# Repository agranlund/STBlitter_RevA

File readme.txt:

----------------------------------------------------------------

A simple Blitter + IDE + 256k ROM decoding board for Atari ST(M)
(c) 2019 Anders Granlund
agranlund@gmail.com

www.happydaze.se

----------------------------------------------------------------

IDE and ROM functionality is based on the work of P.Putnik:
http://atari.8bitchip.info/astide.php

----------------------------------------------------------------

This hardware is provided 'as-is', without any express
or implied warranty. In no event will the authors be held
liable for any damages arising from the use of this hardware.

----------------------------------------------------------------

Notes:

* There are no dependencies between Blitter and ROM+IDE functionality so you can easily
  make a Blitter-only board by leaving out the other parts, or vice versa.

* Bridge 2-3 on both JP1 & JP2 when blitter chip is fitted

* Bridge 1-2 on both JP1 & JP2 when no blitter chip is fitted

* Solder-jumpers SJ1 & SJ2 must always be bridged.
  These are located directly below jumpers JP1 & JP2.

* Resistor R8 is optional and should normally NOT be used.
  If it is used, you must remove Atari ST motherboard resistor R4.
  Atari resistor R4 is a pullup for blitter interrupt (INT3).
  On the ST, this is a 4K7 resistor but on STFM/Mega/STE it has a value of 1K.
  My STBlitter works fine without having to change anything on the ST motherboard,
  but if yours is not then you might want to try changing Atari resistor R4 to a 1K resistor instead.
  Alternatively, just remove it from the Atari and fit a 1K resistor as R8 on STBlitter board.

* EmuTos 0.9.11 will take a very long time to boot if there is no IDE drive is connected.
  This is not a problem on Atari TOS. Nor is it a problem on EmuTos if you have a drive connected.

* The IDE bus is NOT buffered so if you must use cables you need to keep them very short.
  I am using a CF adapter directly plugged into the board without cables and this works fast and reliable.

* The main metal shielding in your ST will probably not fit unless you cut some chunks out of it.
  Perhaps it might fit if you solder the STBlitter directly to the ST motherboard instead of using a socket,
  but I have not tried that - I just run my ST without the metal shielding.

* You will have clearance issues if you are using the 4MB RAM upgrade from Exxos (the one that clips onto the MMU)
  You can solve this by either cutting a small chunk out of the 4MB Ram PCB using a dremel.
  (Make sure to check the underside so you know where the nearest traces are and how much you can cut!)
  Or just stack 2 CPU sockets on the ST motherboard to gain some height and clearance that way.

* The PCB is made from 4 layers according to design rules of Elecrow PCB service (www.elecrow.com)
  The exported Gerbers were done so according to how Elecrow want them so they may or may not be directly
  acceptable to other PCB manufacturers.

Installation:
---------------------------------------------------------------

- Desolder CPU from Atari motherboard and fit a 0.9" DIP4 socket instead.
  CPU is instead installed on the STBlitter board

- IDE: Wire from STBlitter-ACSI10 to pin 10 of ACSI interface (J2) on Atari ST motherboard

- Blitter: Wire from STBlitter-BIRQ to pin 25 of 68901 (U11) on Atari ST motherboard (or the correct side of
  the nearby resistor R4 if you rather solder to that)

- ROM decoding:
  Wiring for 256k ROM decoding will depend on how you modded your ST to fit 256k 2chip roms.
  Of course, you can ignore this step if you don't need ROM decoding or if you already have it from another expansion board.

- Wire from STBlitter-RCEI to ROM2 or CE from Glue.

- Wire from STBlitter-RCEO to CE for the ROMS.

I am using a self made Tos ROM board for holding the EEPROMS:
https://github.com/agranlund/STRom

Parts:
---------------------------------------------------------------

-- Common --
C3, C4        : 0.1uF
CPU Socket    : 2x 0.9" DIP64, digikey: ED90061-ND
ST connector  : 2x 32pin lathed male headers for connecting to socket on ST motherboard
                I use these, but you can of course find them on Digikey or elsewhere:
                https://www.electrokit.com/en/product/male-header-1x40p-lathed-breakable/
Pin headers   : Standard 2.52mm male headers for JP1, JP2 and (ACSI,RCEO,RECI,BIRQ) connector.
                (or ignore this and just solder instead)
Pin Jumper    : 2p jumper for JP1 & JP2 each    
                (or ignore this and just solder instead)

-- Blitter --

R8            : - DO NOT USE -
R1, R2        : 4K7
C1, C2        : 0.1uF
Socket        : PLCC68, digikey: AE10059-ND
Blitter       : You need to find a blitter from somewhere, for example from Exxos:
                https://www.exxoshost.co.uk/atari/last/storenew/

-- IDE & ROM decoding --

74LS03V       : DIP14 package
ATF16V8       : DIP20 package
C5, C6        : 0.1uF
R3            : 4K7
R4, R7        : 2K2
R5            : R390
R6            : R100
LED           : 3mm size
Header        : 2x44-2mm, Digikey: WM18853-ND

CUPL logic for ATF16V8:
----------------------------------------------

Name     STBlitter ;
PartNo   00 ;
Date     2019-09-03 ;
Revision 01 ;
Designer Anders Granlund ;
Company  HappyDaze ;
Assembly None ;
Location  ;
Device   g16v8 ;

/*
 A23     I [ 1     20 ] VCC 
 A22     I [ 2     19 ] T*    RCEI
 A21     I [ 3     18 ] T     RCEO
 A20     I [ 4     17 ] T     DTACK
 A19     I [ 5     16 ] T     IDE_WR
 A18     I [ 6     15 ] T     IDE_RD
 A17     I [ 7     14 ] T     IDE_CS1
 A16     I [ 8     13 ] T     IDE_CS0
 A5      I [ 9     12 ] T*    RW
       GND [ 10    11 ] I     AS
*/

/************ Inputs ************/

pin 1 = A23;
pin 2 = A22;
pin 3 = A21;
pin 4 = A20;
pin 5 = A19;
pin 6 = A18;
pin 7 = A17;
pin 8 = A16;
pin 9 = A5;
pin 11 = AS;
pin 12 = RW;
pin 19 = RCEI; 

/************ Outputs ************/

pin 13 = !IDE_CS0;
pin 14 = !IDE_CS1;
pin 15 = !IDE_RD;
pin 16 = !IDE_WR;
pin 17 = DTACK;
pin 18 = !RCEO;

/************ Logic ************/

DTACK = (!AS & A23 & A22 & A21 & !A20 & !A19 & !A18 & RW) # (A23 & A22 & A21 & A20 & !A19 & !A18 & !A17 & !A16);

RCEO = (!AS & A23 & A22 & A21 & !A20 & !A19 & !A18 & RW) # !RCEI;

IDE_CS0 = (A23 & A22 & A21 & A20 & !A19 & !A18 & !A17 & !A16 & !A5);
IDE_CS1 = (A23 & A22 & A21 & A20 & !A19 & !A18 & !A17 & !A16 & A5);

IDE_RD = (!AS & A23 & A22 & A21 & A20 & !A19 & !A18 & !A17 & !A16 & RW);
IDE_WR = (!AS & A23 & A22 & A21 & A20 & !A19 & !A18 & !A17 & !A16 & !RW);

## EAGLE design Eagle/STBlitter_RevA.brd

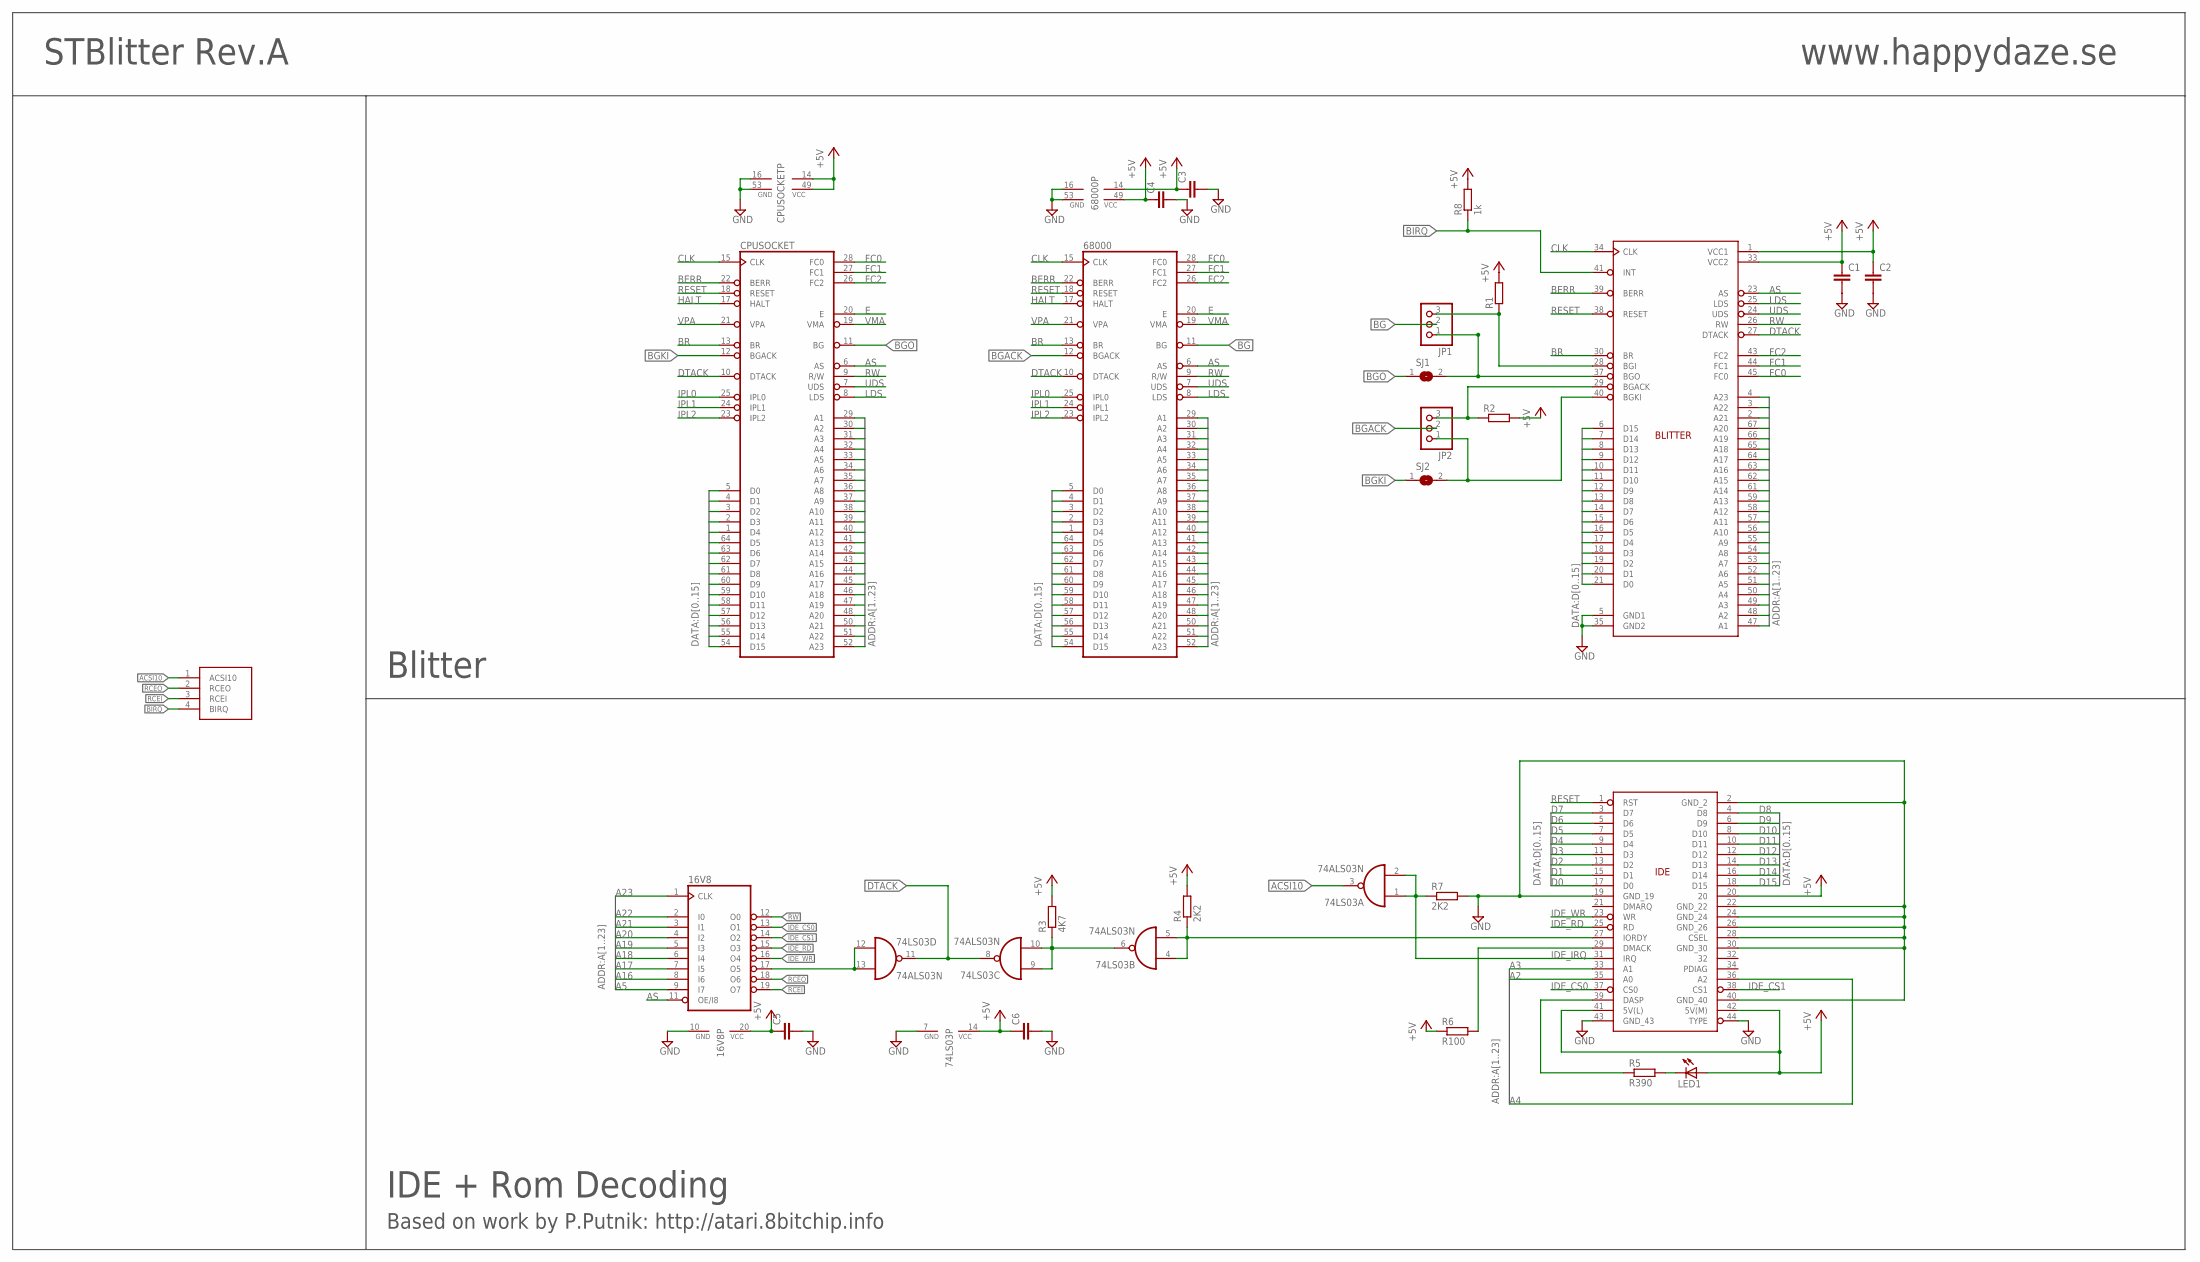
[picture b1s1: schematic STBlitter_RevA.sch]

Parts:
16V8: 16V8; DIL20
74LS03: 74ALS03N; DIL14
68000: MC68000P; DIL64
C1, C2, C3, C4, C5, C6: C-EU050-025X075; C050-025X075
CFCARD: IDE44_CON
CPUSOCKET: MC68000P; DIL64
JP1, JP2: PINHD-1X3; 1X03
LED1: LED3MM
R1, R2: R-EU_0207/12; 0207/12
R3: 4K7; 0207/12
R4, R7: 2K2; 0207/12
R5: R390; 0207/12
R6: R100; 0207/12
R8: 1k; 0207/12
SJ1, SJ2: SJ
U$1: STBLITTER; S68
U$2: XCON

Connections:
+5V: 16V8.20 (VCC), 74LS03.14 (VCC), 68000.14 (VCC), 68000.49 (VCC), C1.1, C2.1, C3.1, C4.1, C5.1, C6.1, CFCARD.20, CFCARD.41 (5V(L)), CFCARD.42 (5V(M)), CPUSOCKET.14 (VCC), CPUSOCKET.49 (VCC), LED1.A, R1.2, R2.2, R3.2, R4.2, R6.1, R8.2, U$1.1 (VCC1), U$1.33 (VCC2)
A1: 68000.29 (A1), CPUSOCKET.29 (A1), U$1.47 (A1)
A2: 68000.30 (A2), CFCARD.35 (A0), CPUSOCKET.30 (A2), U$1.48 (A2)
A3: 68000.31 (A3), CFCARD.33 (A1), CPUSOCKET.31 (A3), U$1.49 (A3)
A4: 68000.32 (A4), CFCARD.36 (A2), CPUSOCKET.32 (A4), U$1.50 (A4)
A5: 16V8.9 (I7), 68000.33 (A5), CPUSOCKET.33 (A5), U$1.51 (A5)
A6: 68000.34 (A6), CPUSOCKET.34 (A6), U$1.52 (A6)
A7: 68000.35 (A7), CPUSOCKET.35 (A7), U$1.53 (A7)
A8: 68000.36 (A8), CPUSOCKET.36 (A8), U$1.54 (A8)
A9: 68000.37 (A9), CPUSOCKET.37 (A9), U$1.55 (A9)
A10: 68000.38 (A10), CPUSOCKET.38 (A10), U$1.56 (A10)
A11: 68000.39 (A11), CPUSOCKET.39 (A11), U$1.57 (A11)
A12: 68000.40 (A12), CPUSOCKET.40 (A12), U$1.58 (A12)
A13: 68000.41 (A13), CPUSOCKET.41 (A13), U$1.59 (A13)
A14: 68000.42 (A14), CPUSOCKET.42 (A14), U$1.61 (A14)
A15: 68000.43 (A15), CPUSOCKET.43 (A15), U$1.62 (A15)
A16: 16V8.8 (I6), 68000.44 (A16), CPUSOCKET.44 (A16), U$1.63 (A16)
A17: 16V8.7 (I5), 68000.45 (A17), CPUSOCKET.45 (A17), U$1.64 (A17)
A18: 16V8.6 (I4), 68000.46 (A18), CPUSOCKET.46 (A18), U$1.65 (A18)
A19: 16V8.5 (I3), 68000.47 (A19), CPUSOCKET.47 (A19), U$1.66 (A19)
A20: 16V8.4 (I2), 68000.48 (A20), CPUSOCKET.48 (A20), U$1.67 (A20)
A21: 16V8.3 (I1), 68000.50 (A21), CPUSOCKET.50 (A21), U$1.2 (A21)
A22: 16V8.2 (I0), 68000.51 (A22), CPUSOCKET.51 (A22), U$1.3 (A22)
A23: 16V8.1 (CLK), 68000.52 (A23), CPUSOCKET.52 (A23), U$1.4 (A23)
ACSI10: 74LS03.3 (O), U$2.1 (ACSI10)
AS: 16V8.11 (OE/I8), 68000.6 (AS), CPUSOCKET.6 (AS), U$1.23 (AS)
BERR: 68000.22 (BERR), CPUSOCKET.22 (BERR), U$1.39 (BERR)
BG: 68000.11 (BG), JP1.2
BGACK: 68000.12 (BGACK), JP2.2
BGKI: CPUSOCKET.12 (BGACK), SJ2.1
BGO: CPUSOCKET.11 (BG), SJ1.1
BIRQ: R8.1, U$1.41 (INT), U$2.4 (BIRQ)
BLTBGI: JP1.3, R1.1, U$1.28 (BGI)
BR: 68000.13 (BR), CPUSOCKET.13 (BR), U$1.30 (BR)
CLK: 68000.15 (CLK), CPUSOCKET.15 (CLK), U$1.34 (CLK)
D0: 68000.5 (D0), CFCARD.17 (D0), CPUSOCKET.5 (D0), U$1.21 (D0)
D1: 68000.4 (D1), CFCARD.15 (D1), CPUSOCKET.4 (D1), U$1.20 (D1)
D2: 68000.3 (D2), CFCARD.13 (D2), CPUSOCKET.3 (D2), U$1.19 (D2)
D3: 68000.2 (D3), CFCARD.11 (D3), CPUSOCKET.2 (D3), U$1.18 (D3)
D4: 68000.1 (D4), CFCARD.9 (D4), CPUSOCKET.1 (D4), U$1.17 (D4)
D5: 68000.64 (D5), CFCARD.7 (D5), CPUSOCKET.64 (D5), U$1.16 (D5)
D6: 68000.63 (D6), CFCARD.5 (D6), CPUSOCKET.63 (D6), U$1.15 (D6)
D7: 68000.62 (D7), CFCARD.3 (D7), CPUSOCKET.62 (D7), U$1.14 (D7)
D8: 68000.61 (D8), CFCARD.4 (D8), CPUSOCKET.61 (D8), U$1.13 (D8)
D9: 68000.60 (D9), CFCARD.6 (D9), CPUSOCKET.60 (D9), U$1.12 (D9)
D10: 68000.59 (D10), CFCARD.8 (D10), CPUSOCKET.59 (D10), U$1.11 (D10)
D11: 68000.58 (D11), CFCARD.10 (D11), CPUSOCKET.58 (D11), U$1.10 (D11)
D12: 68000.57 (D12), CFCARD.12 (D12), CPUSOCKET.57 (D12), U$1.9 (D12)
D13: 68000.56 (D13), CFCARD.14 (D13), CPUSOCKET.56 (D13), U$1.8 (D13)
D14: 68000.55 (D14), CFCARD.16 (D14), CPUSOCKET.55 (D14), U$1.7 (D14)
D15: 68000.54 (D15), CFCARD.18 (D15), CPUSOCKET.54 (D15), U$1.6 (D15)
DTACK: 74LS03.8 (O), 74LS03.11 (O), 68000.10 (DTACK), CPUSOCKET.10 (DTACK), U$1.27 (DTACK)
E: 68000.20 (E), CPUSOCKET.20 (E)
FC0: 68000.28 (FC0), CPUSOCKET.28 (FC0), U$1.45 (FC0)
FC1: 68000.27 (FC1), CPUSOCKET.27 (FC1), U$1.44 (FC1)
FC2: 68000.26 (FC2), CPUSOCKET.26 (FC2), U$1.43 (FC2)
GND: 16V8.10 (GND), 74LS03.7 (GND), 68000.16 (GND), 68000.53 (GND), C1.2, C2.2, C3.2, C4.2, C5.2, C6.2, CFCARD.2 (GND_2), CFCARD.19 (GND_19), CFCARD.22 (GND_22), CFCARD.24 (GND_24), CFCARD.26 (GND_26), CFCARD.28 (CSEL), CFCARD.30 (GND_30), CFCARD.40 (GND_40), CFCARD.43 (GND_43), CFCARD.44 (TYPE), CPUSOCKET.16 (GND), CPUSOCKET.53 (GND), R7.2, U$1.5 (GND1), U$1.35 (GND2)
HALT: 68000.17 (HALT), CPUSOCKET.17 (HALT)
IDE_CS0: 16V8.13 (O1), CFCARD.37 (CS0)
IDE_CS1: 16V8.14 (O2), CFCARD.38 (CS1)
IDE_IRQ: 74LS03.1 (I0), 74LS03.2 (I1), CFCARD.31 (IRQ), R7.1
IDE_RD: 16V8.15 (O3), CFCARD.25 (RD)
IDE_WR: 16V8.16 (O4), CFCARD.23 (WR)
IPL0: 68000.25 (IPL0), CPUSOCKET.25 (IPL0)
IPL1: 68000.24 (IPL1), CPUSOCKET.24 (IPL1)
IPL2: 68000.23 (IPL2), CPUSOCKET.23 (IPL2)
LDS: 68000.8 (LDS), CPUSOCKET.8 (LDS), U$1.25 (LDS)
unnamed: 16V8.17 (O5), 74LS03.12 (I0), 74LS03.13 (I1)
unnamed: 74LS03.6 (O), 74LS03.9 (I0), 74LS03.10 (I1), R3.1
unnamed: 74LS03.4 (I0), 74LS03.5 (I1), CFCARD.27 (IORDY), R4.1
unnamed: CFCARD.29 (DMACK), R6.2
unnamed: CFCARD.39 (DASP), R5.1
unnamed: LED1.K (C), R5.2
RCEI: 16V8.19 (O7), U$2.3 (RCEI)
RCEO: 16V8.18 (O6), U$2.2 (RCEO)
RESET: 68000.18 (RESET), CFCARD.1 (RST), CPUSOCKET.18 (RESET), U$1.38 (RESET)
RW: 16V8.12 (O0), 68000.9 (R/W), CPUSOCKET.9 (R/W), U$1.26 (RW)
UDS: 68000.7 (UDS), CPUSOCKET.7 (UDS), U$1.24 (UDS)
VMA: 68000.19 (VMA), CPUSOCKET.19 (VMA)
VPA: 68000.21 (VPA), CPUSOCKET.21 (VPA)
_BGACK: JP2.3, R2.1, U$1.29 (BGACK)
_BGKI: JP2.1, SJ2.2, U$1.40 (BGKI)
_BGO: JP1.1, SJ1.2, U$1.37 (BGO)

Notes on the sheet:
STBlitter Rev.A
www.happydaze.se
Blitter
IDE + Rom Decoding
Based on work by P.Putnik: http://atari.8bitchip.info

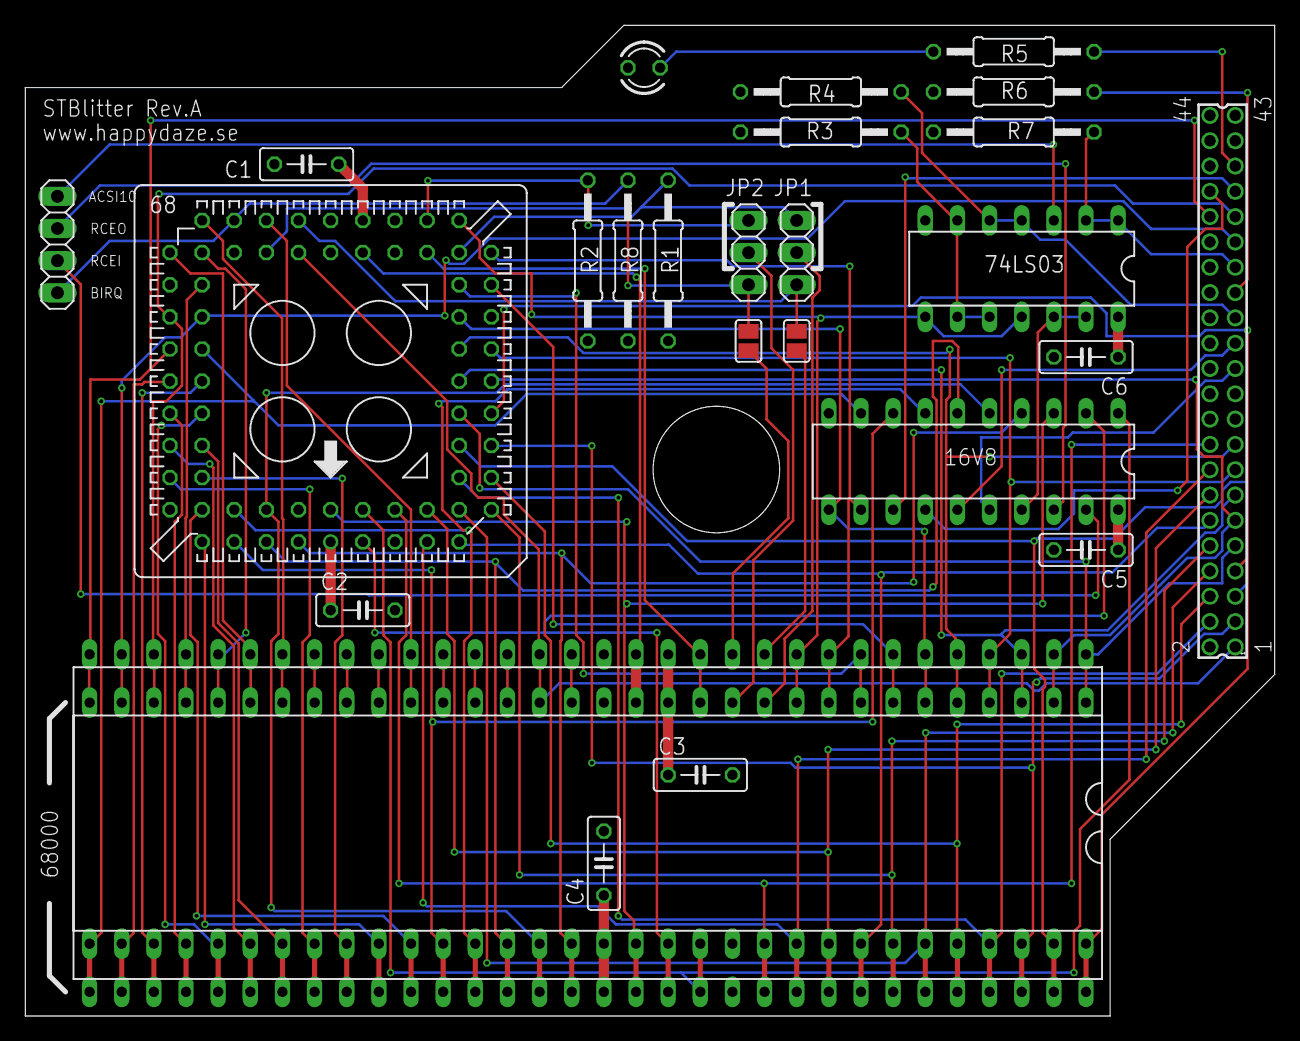
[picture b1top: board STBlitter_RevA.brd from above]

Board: 4 copper layers, 98.7 x 78.3 mm, 26 parts (0 on the bottom side), 83 nets.
